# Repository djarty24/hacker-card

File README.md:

# NFC Hacker Card

This is a hacker card I made for myself!

Front of Card:

Back of Card:

### Description

I mainly used [this article from Hack Club](https://jams.hackclub.com/jam/hacker-card) as a starting point, but my project branched out in several ways. First, I used KiCad instead of EasyEDA. I choose to add two additional LEDs, and I also manually designed the NFC antenna. I learned a lot from this project like how to pick out hardware, what energy harvesting is, reading datasheets to find the capacitor I should use, and actually doing calculations for the resistance values based on the hardware I was using and how bright I wanted the circuit to be.

How it works is when you tap your phone to the card, the phone emits a small magnetic field. The antenna essentially converts this energy  into electricity, which then is harvested by the capacitor to light up the three LEDs on the board. Then, the NFC chip will also use some of that electricity to transmit a link to my website directly to the phone without needing a battery.

### Schematic

### Final Project Cost

#### BOM
### Bill of Materials (BOM) & Cost Breakdown

| Link | Component | Footprint / Package | LCSC Part # | Qty (Total) | Total Cost |
| :--- | :--- | :--- | :--- | :--- | :--- |
| [Link](https://jlcpcb.com/partdetail/21832-CL10B224KA8NNNC/C21120) | 220nF | 0603 | C21120 | 5 | $0.0835 |
| [Link](https://jlcpcb.com/partdetail/Hubei_KENTOElec-KT0805Y/C2296) | KT-0805Y (Yellow LED) | 0805 | C2296 | 15 | $0.2280 |
| [Link](https://jlcpcb.com/partdetail/VikingTech-AR03FTC1500/C234295) | 150Ω Resistor | 0603 | C22808 | 15 | ~$0.03 |
| [Link](https://jlcpcb.com/partdetail/NXPSemicon-NT3H2111W0FHKH/C710403) | NT3H2111W0FHKH (NFC Chip) | XQFN-8 | C710403 | 5 | $3.2115 |

Please Note: The individual component costs listed above aren't completely accurate. Because I used JLCPCB for the full assembly (which was required for the specific surface-mount parts I chose and ended up being the cheapest option overall) the individual component prices don't matter as much as the final fabricated total.

#### JLCPCB Price Estimate

After submitting all of the info (gerber files, bom.csv, and positions.csv) to JLCPCB for assembly, this was the final price estimate I got.

**PCB Prototype (Fabrication):** $2.00
**Economic PCBA (Assembly):** $16.52
**Estimated Shipping:** $9.44
**Total Price:** **$27.96**

<hr>

This project was made for Hack Club's Forge!

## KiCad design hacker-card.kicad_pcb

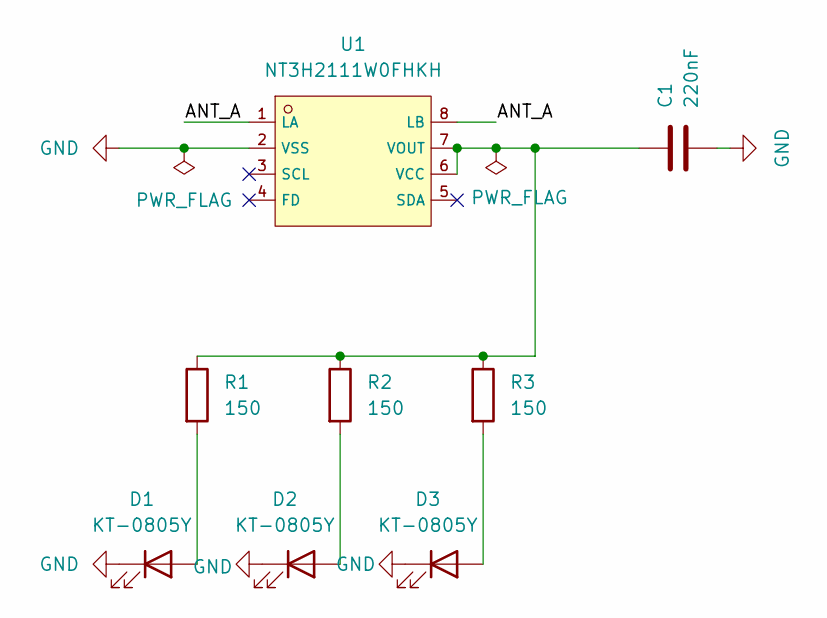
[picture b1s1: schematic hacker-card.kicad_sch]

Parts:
C1: 220nF; C_0603_1608Metric
D1, D2, D3: KT-0805Y; LED_0805_2012Metric
R1, R2, R3: 150; R_0603_1608Metric
U1: NT3H2111W0FHKH; XQFN-8_L1.6-W1.6-P0.50-BL_NT3H2111W0FHKH; LCSC C710403

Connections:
/ANT_A: U1.1 (LA), U1.8 (LB)
GND: C1.2, D1.1 (K), D2.1 (K), D3.1 (K), U1.2 (VSS)
unnamed: D1.2 (A), R1.2
unnamed: D2.2 (A), R2.2
unnamed: D3.2 (A), R3.2
unnamed: C1.1, R1.1, R2.1, R3.1, U1.6 (VCC), U1.7 (VOUT)

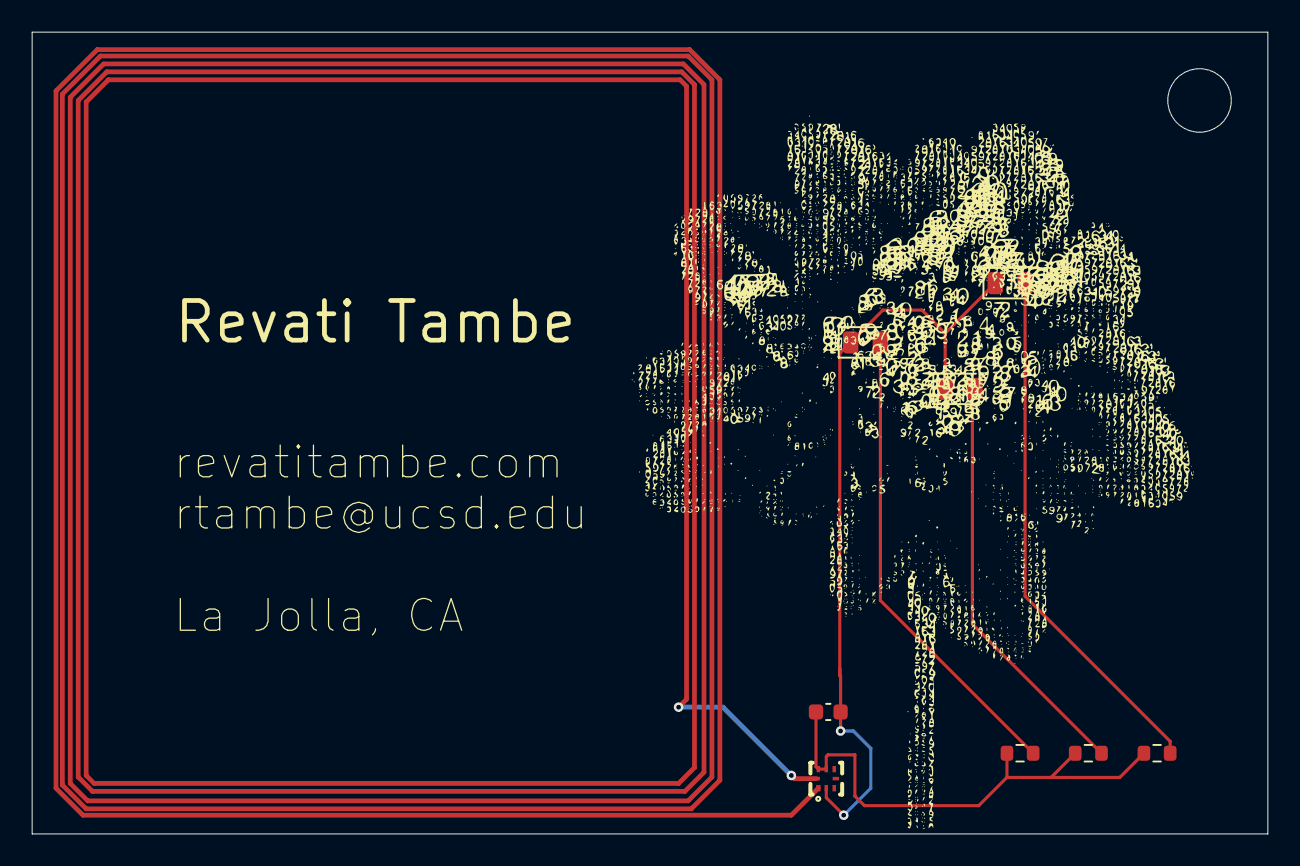
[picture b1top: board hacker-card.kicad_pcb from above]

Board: 2 copper layers, 77.8 x 50.5 mm, 9 parts (0 on the bottom side), 6 nets.

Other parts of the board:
.: LOGO

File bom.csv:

Designator,Component Value / Name,Footprint / Package,LCSC Part #,Qty (Total),Total Cost
C1,220nF,0603,C21120,5,$0.0835
"D1, D2, D3",KT-0805Y (Yellow LED),0805,C2296,15,$0.2280
"R1, R2, R3",150Ω Resistor,0603,C22808,15,$0.03
U1,NT3H2111W0FHKH (NFC Chip),XQFN-8,C710403,5,$3.2115
